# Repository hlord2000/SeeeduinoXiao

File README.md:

# Seeeduino XIAO Project Template

This KiCAD Template simplifies initial setup for Seeeduino XIAO or Adafruit QT Py PCB designs.

To begin, clone this repository to your KICAD_USER_TEMPLATE_DIR as found under "Preferences > Configure Paths..."

Next, use "File > New Project from Template..." or "Ctrl+T" and select "User Templates." Select the template and begin!

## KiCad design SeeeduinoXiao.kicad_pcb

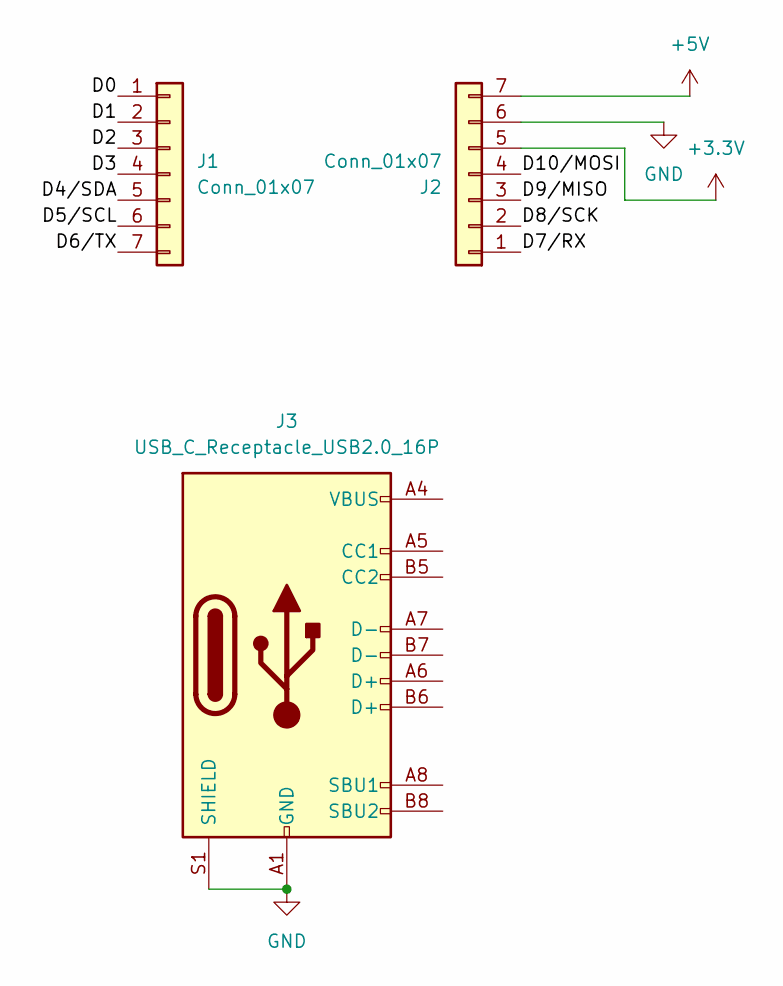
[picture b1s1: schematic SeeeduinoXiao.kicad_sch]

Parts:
J1, J2: Conn_01x07; H7-HALF-HOLE-2.54
J3: USB_C_Receptacle_USB2.0_16P; USB_C_Receptacle_HRO_TYPE-C-31-M-12

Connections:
+3.3V: J2.5
+5V: J2.7
/D0: J1.1
/D1: J1.2
/D2: J1.3
/D3: J1.4
/D4/SDA: J1.5
/D5/SCL: J1.6
/D6/TX: J1.7
/D7/RX: J2.1
/D8/SCK: J2.2
/D9/MISO: J2.3
/D10/MOSI: J2.4
GND: J2.6, J3.A1 (GND), J3.A12 (GND), J3.B1 (GND), J3.B12 (GND), J3.S1 (SHIELD)
unnamed: J3.A4 (VBUS), J3.A9 (VBUS), J3.B4 (VBUS), J3.B9 (VBUS)

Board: 2 copper layers, 3 parts (0 on the bottom side), 2 nets, no tracks yet.

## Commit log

2024-03-23 Initial commit.
